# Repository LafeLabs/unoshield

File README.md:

# unoshield
generic uno shield

## UNO Shield for multiple applicaitons

Multiple Application Uno Shield = MAUS

| description   |  part number | number | link |
|---------------|--------------|--------|------|
|  Buttons      |              |    2   |[digikey]()| 
|   switch      |              |    1   |[digikey]() |
|   Big Cap     | ~399-6558-ND~  |    1   |[digikey]()|
| big cap |1189-1745-ND|1|[digikey]()|
| spring clips | 277-6354-ND   |    3   | [digikey](https://www.digikey.com/product-detail/en/infineon-technologies/IRF7862TRPBF/IRF7862TRPBFCT-ND/1925918) |
|  20k pot      |              |    1   |[digikey]()|
|  4 pin header |              |    2   |[digikey]()|
|  5 pin header |              |    1   |[digikey]()|
|    Transistor |  IRF7862     |    1   |[mouser](https://www.mouser.com/ProductDetail/Infineon-IR/IRF7862TRPBF?qs=%2fha2pyFadughaNBoB2VyeDpq8vz8zxt1%252baAF1EqMLy8%3d)| 
|diode| S1BFSCT-ND | 1|[digikey](https://www.digikey.com/product-detail/en/on-semiconductor/S1B/S1BFSCT-ND/965719)|
|8 pin socket ||||
|10 pin socket||||
|6 pin socket ||||
|10k resistor ||2||
|300 ohms     ||1||

### Applications

 - simple control of stepper motor with speed knob and buttons
 - temperature control with thermometer and heater
 - blinking lights neopixel
 - vibrational motor
 - trash stepper
 -

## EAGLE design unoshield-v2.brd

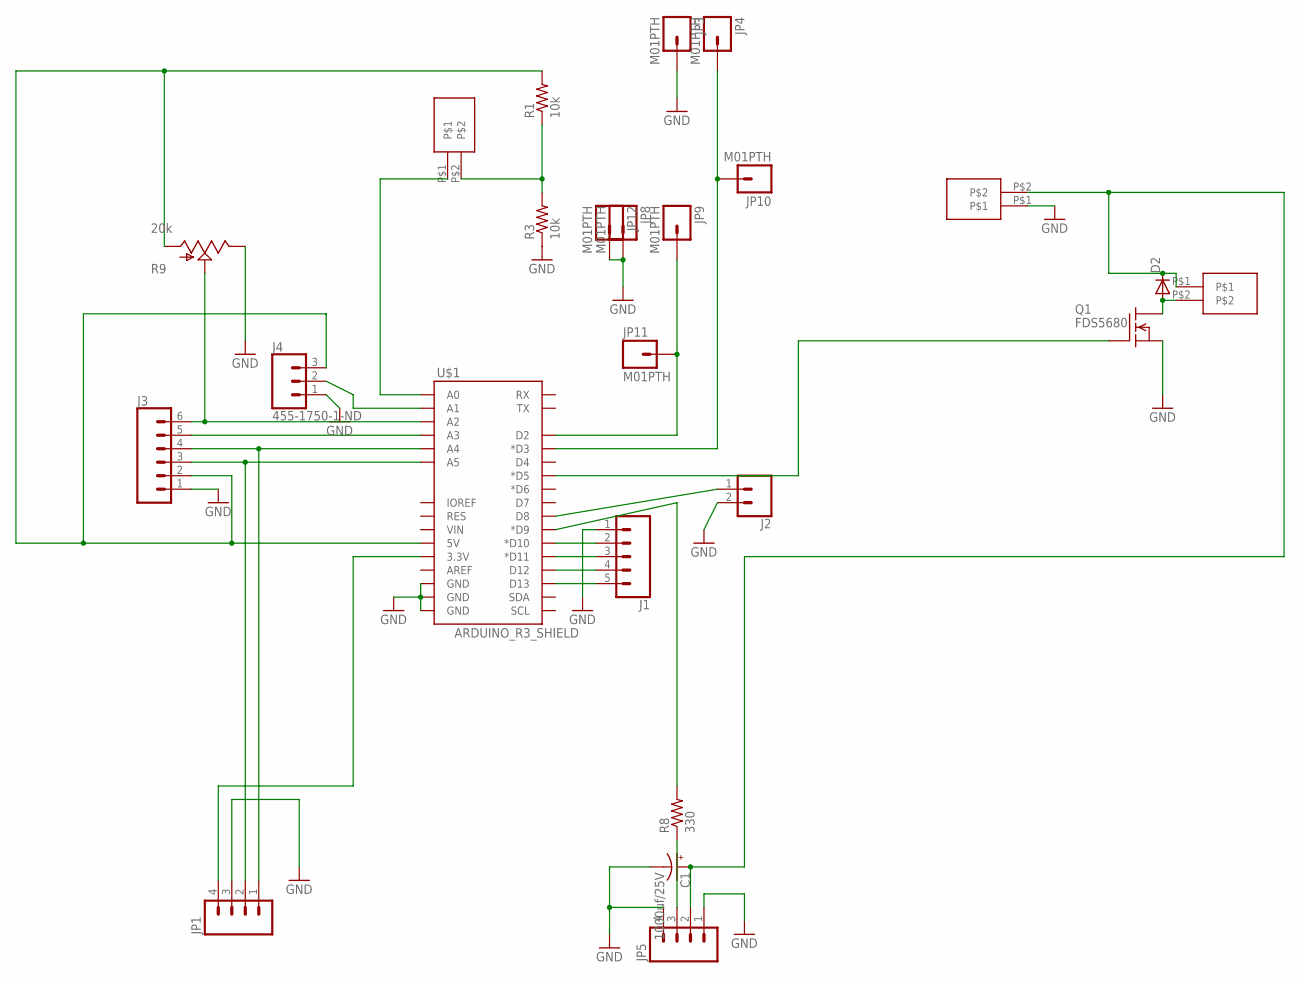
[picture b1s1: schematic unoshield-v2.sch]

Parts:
C1: 1000uf/25V; CPOL-RADIAL-1000UF-25V-KIT
D2: DIODE-DO-214AC; DO-214AC
J1: CONN_05; 1X05
J2: CONN_02; 1X02
J3: CONN_06SILK_FEMALE_PTH; 1X06
J4: 455-1750-1-ND; 1X03
JP1, JP5: M04PTH; 1X04
JP3, JP4, JP8, JP9, JP10, JP11, JP12: M01PTH; 1X01
Q1: FDS5680; SO-8
R1, R3: 10k; R0603
R8: 330; R0603
R9: 20k; ALPS_POT_KIT
U$1: ARDUINO_R3_SHIELD; UNO_R3_SHIELD
U$6: SPRING-TERMINAL
X1, X2: SPRING-TERMINAL

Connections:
5V: J3.2, J4.3, R1.2, R9.P$3 (A), U$1.5V
BUTTON: JP4.1, JP10.1, U$1.D3 (*D3)
CL: J3.3, JP1.2, U$1.A5
DA: J3.4, JP1.1, U$1.A4
GND: C1.-, J1.1, J2.2, J3.1, J4.1, JP1.3, JP3.1, JP5.1, JP5.4, JP8.1, JP12.1, Q1.1 (S), Q1.2 (S), Q1.3 (S), R3.1, R9.P$1 (E), U$1.GND@0 (GND), U$1.GND@1 (GND), U$1.GND@2 (GND), X1.P$1
unnamed: Q1.4 (G), U$1.D5 (*D5)
unnamed: R8.2, U$1.D9 (*D9)
unnamed: R1.1, R3.2, X2.P$2
unnamed: J4.2, U$1.A1
unnamed: J1.2, U$1.D10 (*D10)
unnamed: D2.A, Q1.5 (D), Q1.6 (D), Q1.7 (D), Q1.8 (D), U$6.P$2
unnamed: J1.3, U$1.D11 (*D11)
unnamed: J1.4, U$1.D12
unnamed: J1.5, U$1.D13
unnamed: JP9.1, JP11.1, U$1.D2
unnamed: J2.1, U$1.D8
unnamed: J3.5, U$1.A3
unnamed: U$1.A0, X2.P$1
unnamed: JP5.3, R8.1
unnamed: J3.6, R9.P$2 (S), U$1.A2
VCC: JP1.4, U$1.3.3V
VIN: C1.+, D2.C, JP5.2, U$6.P$1, X1.P$2

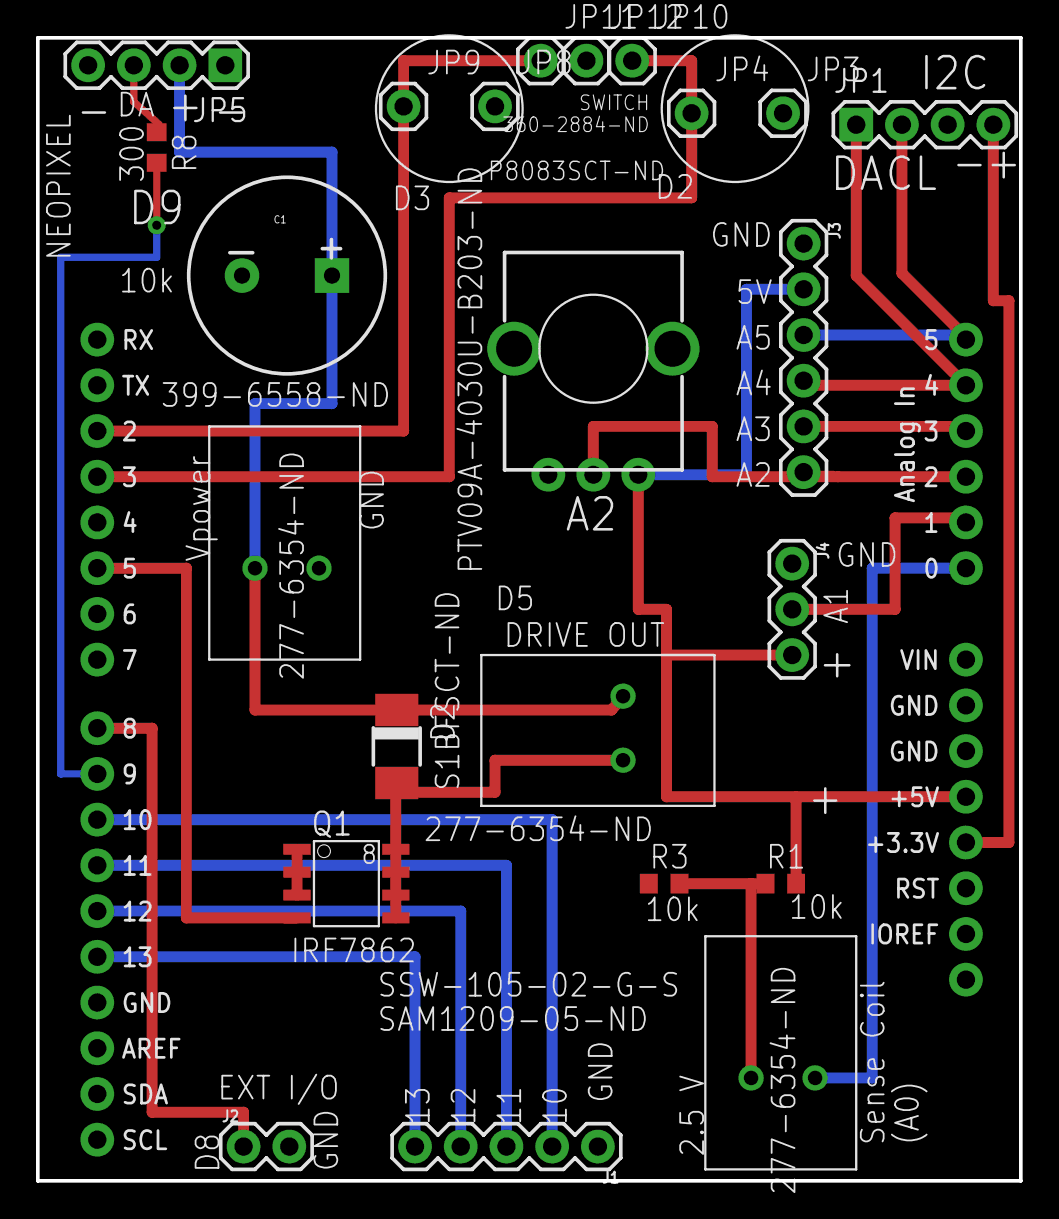
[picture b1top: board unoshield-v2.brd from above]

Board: 2 copper layers, 54.6 x 63.5 mm, 24 parts (0 on the bottom side), 22 nets.

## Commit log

2019-01-26 shield quite possibly done and ready to order now
2019-01-27 updating readme.md from trashrobot.org
2019-01-31 added external digital I/O line
2019-03-10 uno shield design work
2019-03-15 put larger voltage cap on the power supply

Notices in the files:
unoshield-v2.brd:
PUBLIC DOMAIN
parts and their libraries:
SparkFun-Boards: Licensing: Creative Commons ShareAlike 4.0 International - https://creativecommons.org/licenses/by-sa/4.0
